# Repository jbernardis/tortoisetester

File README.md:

Circuit schematics and case design for a battery operated portable tortoise tester for tortoise show mothion switch machines

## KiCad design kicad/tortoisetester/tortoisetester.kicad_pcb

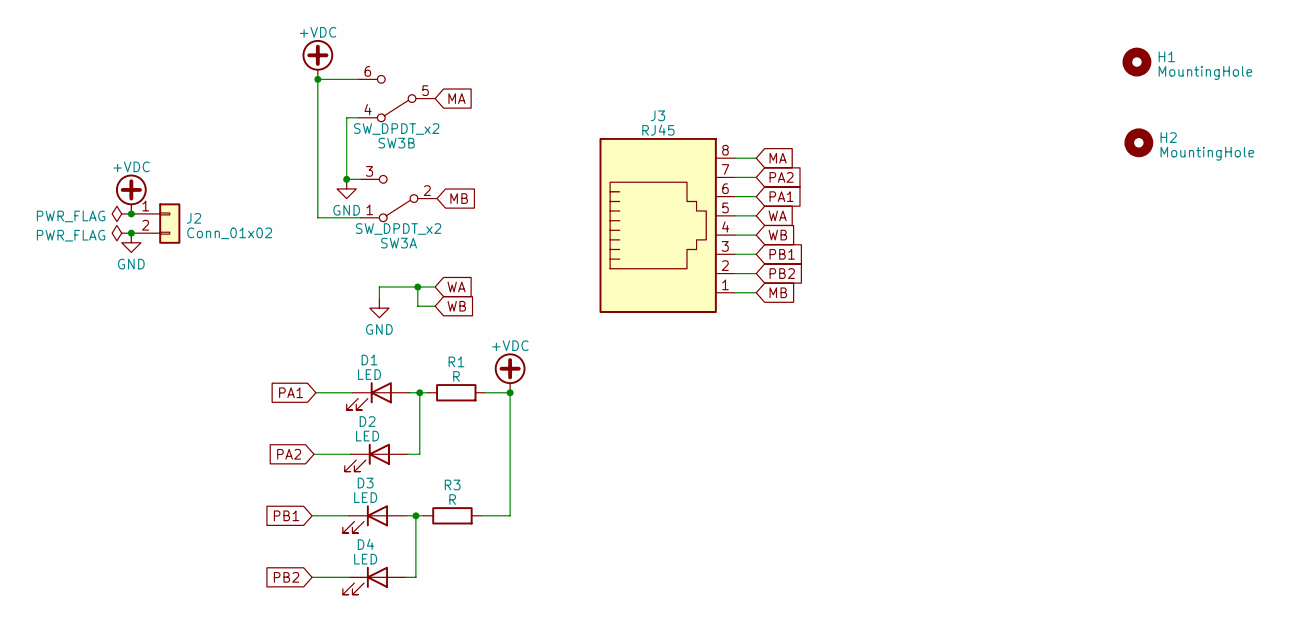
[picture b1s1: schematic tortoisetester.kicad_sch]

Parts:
D1, D2, D3, D4: LED; LED_D5.0mm
H1, H2: MountingHole; MountingHole_3.2mm_M3
J2: Conn_01x02; PinHeader_1x02_P2.54mm_Vertical
J3: RJ45; RJ45_Amphenol_54602-x08_Horizontal
R1, R3: R; R_Axial_DIN0309_L9.0mm_D3.2mm_P12.70mm_Horizontal
SW3: SW_DPDT_x2; DPDT Switch PTH

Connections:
+VDC: J2.1, R1.2, R3.2, SW3.1 (A), SW3.6 (C)
MA: J3.8, SW3.5 (B)
MB: J3.1, SW3.2 (B)
unnamed: D1.2 (A), D2.2 (A), R1.1
unnamed: D3.2 (A), D4.2 (A), R3.1
PA1: D1.1 (K), J3.6
PA2: D2.1 (K), J3.7
PB1: D3.1 (K), J3.3
PB2: D4.1 (K), J3.2
WA: J2.2, J3.4, J3.5, SW3.3 (C), SW3.4 (A)

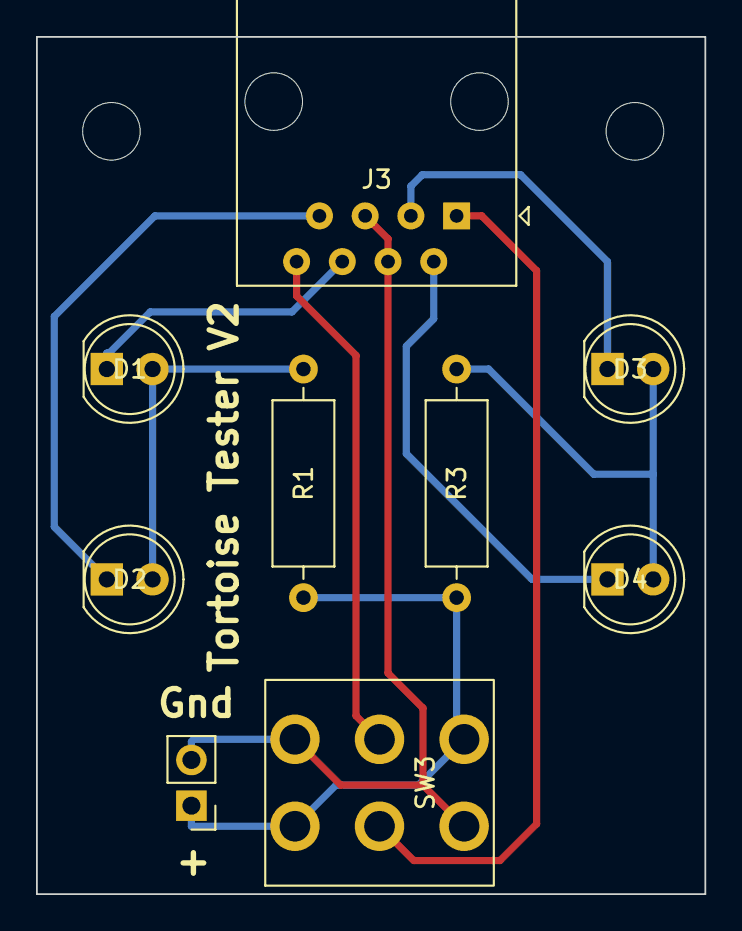
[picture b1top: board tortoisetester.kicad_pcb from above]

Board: 2 copper layers, 37.1 x 47.6 mm, 11 parts (0 on the bottom side), 10 nets.

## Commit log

2023-11-11 cleanup - adding footprint for DPDT switch
